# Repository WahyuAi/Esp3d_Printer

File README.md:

# Esp3d Printer

Simple 3D printer board based on ESP32.

## Schematic

## PCB View

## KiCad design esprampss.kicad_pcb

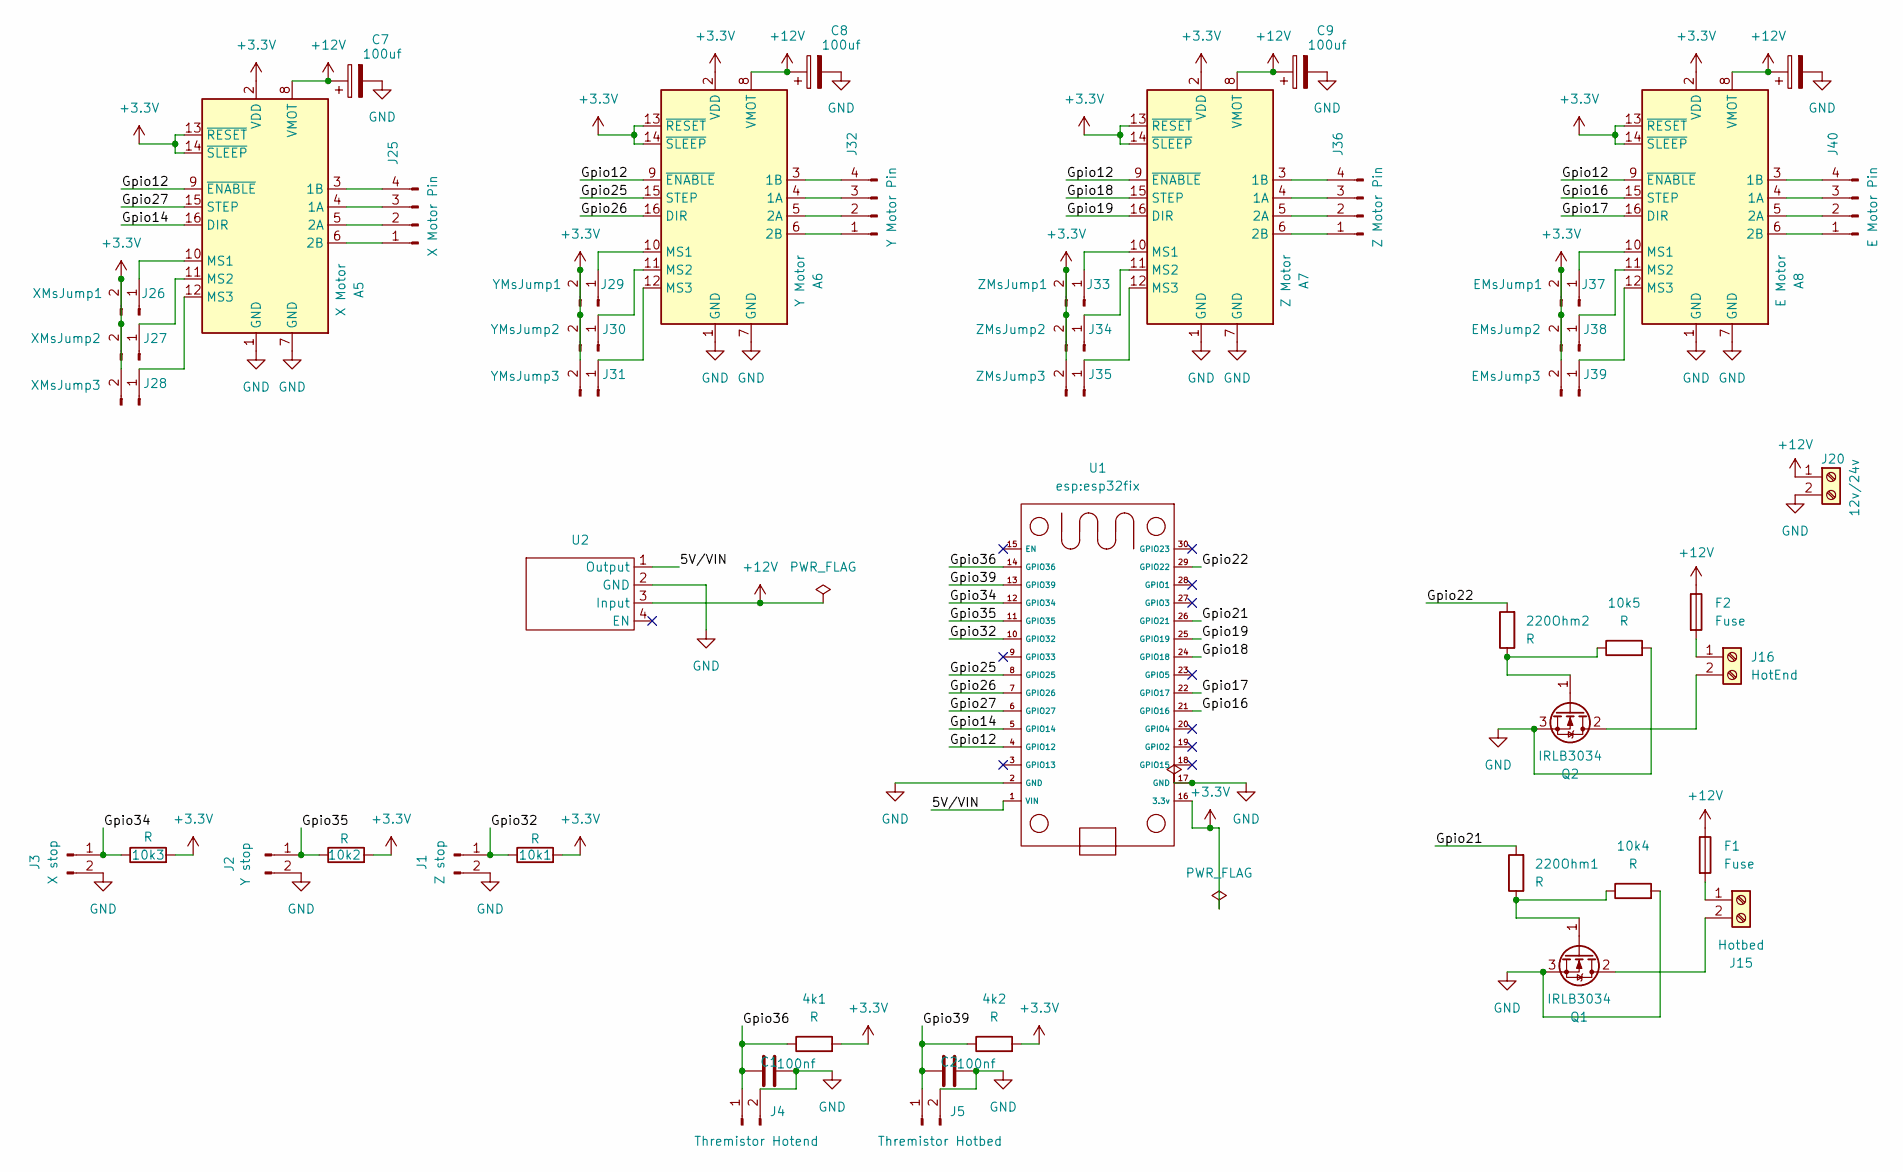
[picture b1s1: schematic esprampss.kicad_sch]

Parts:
4k1, 4k2, 10k1, 10k2, 10k3, 10k4, 10k5, 220Ohm1, 220Ohm2: R; R_Axial_DIN0207_L6.3mm_D2.5mm_P10.16mm_Horizontal
A5: X Motor; Pololu_Breakout-16_15.2x20.3mm
A6: Y Motor; Pololu_Breakout-16_15.2x20.3mm
A7: Z Motor; Pololu_Breakout-16_15.2x20.3mm
A8: E Motor; Pololu_Breakout-16_15.2x20.3mm
C1, C2: 100nf; C_Disc_D5.0mm_W2.5mm_P2.50mm
C6, C7, C8, C9: 100uf; CP_Radial_D4.0mm_P2.00mm
F1, F2: Fuse; Fuseholder_Cylinder-5x20mm_Stelvio-Kontek_PTF78_Horizontal_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
J1: Z stop; PinHeader_1x02_P2.54mm_Vertical
J2: Y stop; PinHeader_1x02_P2.54mm_Vertical
J3: X stop; PinHeader_1x02_P2.54mm_Vertical
J4: Thremistor Hotend; PinHeader_1x02_P2.54mm_Vertical
J5: Thremistor Hotbed; PinHeader_1x02_P2.54mm_Vertical
J15: Hotbed; TerminalBlock_CUI_TB007-508-02_1x02_P5.08mm_Horizontal
J16: HotEnd; TerminalBlock_CUI_TB007-508-02_1x02_P5.08mm_Horizontal
J20: 12v/24v; TerminalBlock_CUI_TB007-508-02_1x02_P5.08mm_Horizontal
J25: X Motor Pin; PinHeader_1x04_P2.54mm_Vertical
J26: XMsJump1; PinHeader_1x02_P2.54mm_Vertical
J27: XMsJump2; PinHeader_1x02_P2.54mm_Vertical
J28: XMsJump3; PinHeader_1x02_P2.54mm_Vertical
J29: YMsJump1; PinHeader_1x02_P2.54mm_Vertical
J30: YMsJump2; PinHeader_1x02_P2.54mm_Vertical
J31: YMsJump3; PinHeader_1x02_P2.54mm_Vertical
J32: Y Motor Pin; PinHeader_1x04_P2.54mm_Vertical
J33: ZMsJump1; PinHeader_1x02_P2.54mm_Vertical
J34: ZMsJump2; PinHeader_1x02_P2.54mm_Vertical
J35: ZMsJump3; PinHeader_1x02_P2.54mm_Vertical
J36: Z Motor Pin; PinHeader_1x04_P2.54mm_Vertical
J37: EMsJump1; PinHeader_1x02_P2.54mm_Vertical
J38: EMsJump2; PinHeader_1x02_P2.54mm_Vertical
J39: EMsJump3; PinHeader_1x02_P2.54mm_Vertical
J40: E Motor Pin; PinHeader_1x04_P2.54mm_Vertical
Q1, Q2: IRLB3034; TO-220-3_Vertical
U1: esp32fix
U2: Module_Buck_Mini360_THT

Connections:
+3.3V: 4k1.2, 4k2.2, 10k1.2, 10k2.2, 10k3.2, A5.2 (VDD), A5.13 (~RESET), A5.14 (~SLEEP), A6.2 (VDD), A6.13 (~RESET), A6.14 (~SLEEP), A7.2 (VDD), A7.13 (~RESET), A7.14 (~SLEEP), A8.2 (VDD), A8.13 (~RESET), A8.14 (~SLEEP), J26.2, J27.2, J28.2, J29.2, J30.2, J31.2, J33.2, J34.2, J35.2, J37.2, J38.2, J39.2, U1.16 (3.3v)
+12V: A5.8 (VMOT), A6.8 (VMOT), A7.8 (VMOT), A8.8 (VMOT), C6.1, C7.1, C8.1, C9.1, F1.1, F2.1, J20.1, U2.3 (Input)
/5V/VIN: U1.1 (VIN), U2.1 (Output)
/Gpio12: A5.9 (~ENABLE), A6.9 (~ENABLE), A7.9 (~ENABLE), A8.9 (~ENABLE), U1.4 (GPIO12)
/Gpio14: A5.16 (DIR), U1.5 (GPIO14)
/Gpio16: A8.15 (STEP), U1.21 (GPIO16)
/Gpio17: A8.16 (DIR), U1.22 (GPIO17)
/Gpio18: A7.15 (STEP), U1.24 (GPIO18)
/Gpio19: A7.16 (DIR), U1.25 (GPIO19)
/Gpio21: 220Ohm1.2, U1.26 (GPIO21)
/Gpio22: 220Ohm2.2, U1.29 (GPIO22)
/Gpio25: A6.15 (STEP), U1.8 (GPIO25)
/Gpio26: A6.16 (DIR), U1.7 (GPIO26)
/Gpio27: A5.15 (STEP), U1.6 (GPIO27)
/Gpio32: 10k1.1, J1.1, U1.10 (GPIO32)
/Gpio34: 10k3.1, J3.1, U1.12 (GPIO34)
/Gpio35: 10k2.1, J2.1, U1.11 (GPIO35)
/Gpio36: 4k1.1, C1.1, J4.1, U1.14 (GPIO36)
/Gpio39: 4k2.1, C2.1, J5.1, U1.13 (GPIO39)
GND: 10k4.2, 10k5.2, A5.1 (GND), A5.7 (GND), A6.1 (GND), A6.7 (GND), A7.1 (GND), A7.7 (GND), A8.1 (GND), A8.7 (GND), C1.2, C2.2, C6.2, C7.2, C8.2, C9.2, J1.2, J2.2, J3.2, J4.2, J5.2, J20.2, Q1.3 (S), Q2.3 (S), U1.2 (GND), U1.17 (GND), U2.2 (GND)
unnamed: A5.4 (1A), J25.3
unnamed: A5.3 (1B), J25.4
unnamed: A5.5 (2A), J25.2
unnamed: A5.6 (2B), J25.1
unnamed: A5.10 (MS1), J26.1
unnamed: A5.11 (MS2), J27.1
unnamed: A5.12 (MS3), J28.1
unnamed: A6.4 (1A), J32.3
unnamed: A6.3 (1B), J32.4
unnamed: A6.5 (2A), J32.2
unnamed: A6.6 (2B), J32.1
unnamed: A6.10 (MS1), J29.1
unnamed: A6.11 (MS2), J30.1
unnamed: A6.12 (MS3), J31.1
unnamed: A7.4 (1A), J36.3
unnamed: A7.3 (1B), J36.4
unnamed: A7.5 (2A), J36.2
unnamed: A7.6 (2B), J36.1
unnamed: A7.10 (MS1), J33.1
unnamed: A7.11 (MS2), J34.1
unnamed: A7.12 (MS3), J35.1
unnamed: A8.4 (1A), J40.3
unnamed: A8.3 (1B), J40.4
unnamed: A8.5 (2A), J40.2
unnamed: A8.6 (2B), J40.1
unnamed: A8.10 (MS1), J37.1
unnamed: A8.11 (MS2), J38.1
unnamed: A8.12 (MS3), J39.1
unnamed: F1.2, J15.1
unnamed: J15.2, Q1.2 (D)
unnamed: F2.2, J16.1
unnamed: J16.2, Q2.2 (D)
unnamed: 10k4.1, 220Ohm1.1, Q1.1 (G)
unnamed: 10k5.1, 220Ohm2.1, Q2.1 (G)

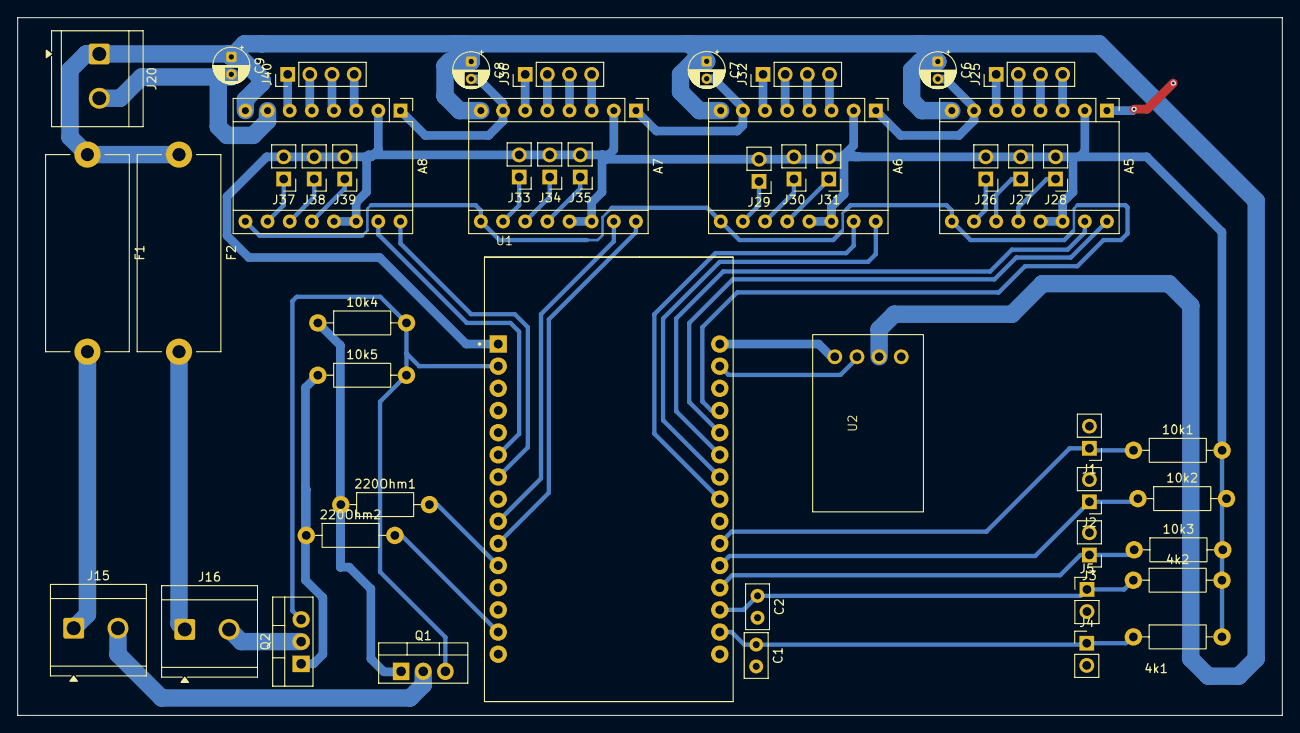
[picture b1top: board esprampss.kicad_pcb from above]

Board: 2 copper layers, 145.0 x 80.0 mm, 49 parts (0 on the bottom side), 54 nets.
